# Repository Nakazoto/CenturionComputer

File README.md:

# CenturionComputer
If you are here reading this readme, most likely you are looking for the Wiki. Click the Wiki link above or the link below to get to there.

https://github.com/Nakazoto/CenturionComputer/wiki

This is just a simple backup of all the files related to the Centurion that I have stored on my HD. The Wiki itself has far more in-depth information about the Centurion and it's individual cards.

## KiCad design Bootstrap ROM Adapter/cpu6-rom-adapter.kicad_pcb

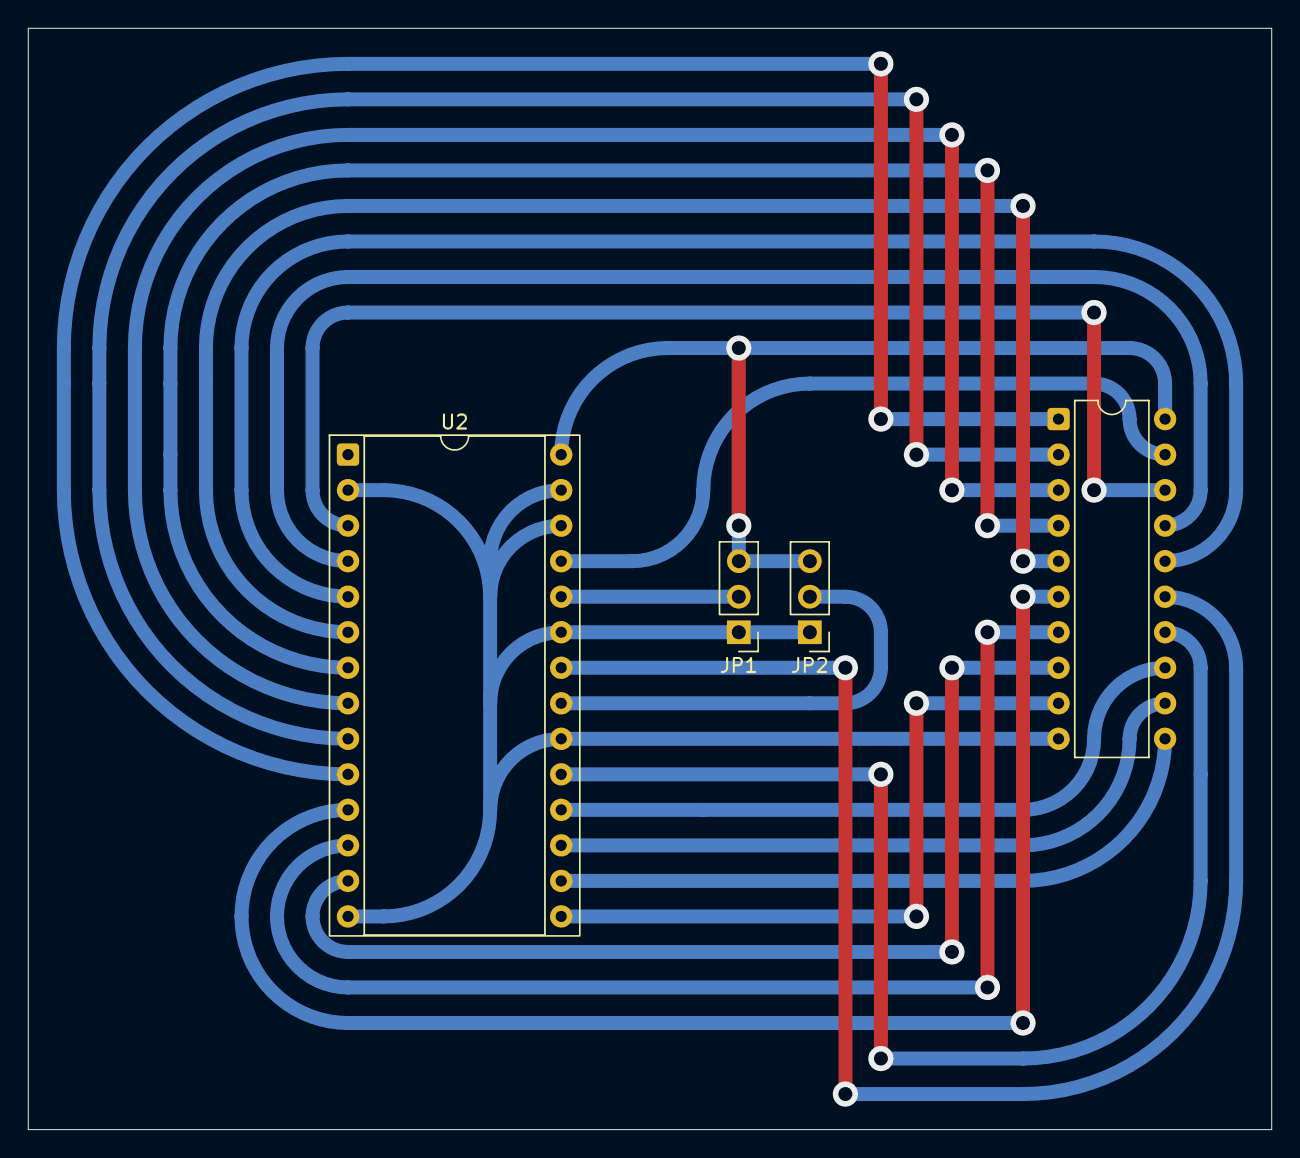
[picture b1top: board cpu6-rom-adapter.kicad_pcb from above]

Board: 2 copper layers, 88.9 x 78.7 mm, 4 parts (0 on the bottom side), 22 nets.

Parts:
J1: Conn_02x10_Counter_Clockwise; DIP-20_W7.62mm
JP1, JP2: Jumper_3_Open; PinHeader_1x03_P2.54mm_Vertical
U2: W27E257; DIP-28_W15.24mm_Socket

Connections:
/A0: J1.1, U2.10 (A0)
/A1: J1.2, U2.9 (A1)
/A2: J1.3, U2.8 (A2)
/A3: J1.4, U2.7 (A3)
/A4: J1.5, U2.6 (A4)
/A5: J1.16, U2.5 (A5)
/A6: J1.17, U2.4 (A6)
/A7: J1.18, U2.3 (A7)
/A8: J1.19, U2.25 (A8)
/A9: JP1.2 (C), U2.24 (A9)
/A10: JP2.2 (C), U2.21 (A10)
/GND: J1.10, JP1.1 (A), JP2.1 (A), U2.2 (A12), U2.14 (GND), U2.20 (~CE), U2.23 (A11), U2.26 (A13), U2.27 (A14)
/Q0: J1.6, U2.11 (Q0)
/Q1: J1.7, U2.12 (Q1)
/Q2: J1.8, U2.13 (Q2)
/Q3: J1.9, U2.15 (Q3)
/Q4: J1.11, U2.16 (Q4)
/Q5: J1.12, U2.17 (Q5)
/Q6: J1.13, U2.18 (Q6)
/Q7: J1.14, U2.19 (Q7)
/Vcc: J1.20, JP1.3 (B), JP2.3 (B), U2.28 (Vcc)
/~G: J1.15, U2.22 (~OE)

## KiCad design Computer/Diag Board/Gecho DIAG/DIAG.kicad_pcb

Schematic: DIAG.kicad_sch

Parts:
C1, C2: 150uF; CP_Axial_L25.0mm_D10.0mm_P30.00mm_Horizontal
C3: 47uF; CP_Axial_L18.0mm_D6.5mm_P25.00mm_Horizontal
C4, C5, C6, C7, C8, C9, C10, C11, C12, C13, C14, C15, C16, C17, C18, C19, C20, C21, C22, C23, C24, C25, C26, C27, C28, C29, C30, C31, C32, C33, C34, C35, C36: 100nF; C_Disc_D3.0mm_W1.6mm_P2.50mm
CR1, CR2, CR3: D; D_DO-35_SOD27_P11.43mm_Horizontal
CR4: LED; LED_D1.8mm_W1.8mm_H2.4mm_Horizontal_O6.35mm_Z1.6mm
J1, J2, J3: SW_SPDT_312; SW_Slide-03_Wuerth-WS-SLTV_10x2.5x6.4_P2.54mm
P1: Edge Connector; BUS_EE200
P2: 26 pin IDC horizontal; IDC-Header_2x13_P2.54mm_Horizontal_TB
R1, R2, R3, R4, R5, R6, R7, R8, R13, R14: 4k7; R_Axial_DIN0207_L6.3mm_D2.5mm_P11.43mm_Horizontal
R9, R10, R23: 330R; R_Axial_DIN0207_L6.3mm_D2.5mm_P11.43mm_Horizontal
R11, R12, R18: 1k; R_Axial_DIN0207_L6.3mm_D2.5mm_P11.43mm_Horizontal
R15, R16, R17: R; R_Axial_DIN0207_L6.3mm_D2.5mm_P11.43mm_Horizontal
R19, R20, R21, R22: 470R; R_Axial_DIN0207_L6.3mm_D2.5mm_P11.43mm_Horizontal
RP1, RP2: 4k7; R_Array_SIP10_cent
TP1, TP2, TP3, TP4: TestPoint; TestPoint_Hex_D2.0mm_Drill0.8mm
UA1: 74LS38; DIP-14_W7.62mm_cent
UA2, UA3, UA4, UA5, UA6: DS8835N; DIP-16_W7.62mm_cent
UA7: 74LS373; DIP-20_W7.62mm_cent
UA8: AM2907; DIP-20_W7.62mm_cent
UAB1: 74LS38; DIP-14_W7.62mm_cent
UB1: 74LS08; DIP-14_W7.62mm_cent
UB2: 74LS109; DIP-16_W7.62mm_cent
UB3, UB4: DS8835N; DIP-16_W7.62mm_cent
UB5: 74LS373; DIP-20_W7.62mm_cent
UB6: SW_DIP_x08; SW_DIP_SPSTx08_Slide_9.78x22.5mm_W8.61mm_P2.54mm_cent
UB7: 74LS37; DIP-14_W7.62mm_cent
UC1, UC7: 74LS74; DIP-14_W7.62mm_cent
UC2: 74LS161; DIP-16_W7.62mm_cent
UC3: 74LS85; DIP-16_W7.62mm_cent
UC4, UC8: 74LS08; DIP-14_W7.62mm_cent
UC5: 74LS670; DIP-16_W7.62mm_cent
UC6: 74LS38; DIP-14_W7.62mm_cent
UD1, UD7: 74LS04; DIP-14_W7.62mm_cent
UD2: 74LS688; DIP-20_W7.62mm_cent
UD3, UD4: 74LS244; DIP-20_W7.62mm_cent
UD5: Z84C00xxP; DIP-40_W15.24mm_cent_socketchip
UD6: 74LS00; DIP-14_W7.62mm_cent
UD8: 74LS74; DIP-14_W7.62mm_cent
UE1: 74LS20; DIP-14_W7.62mm_cent
UE2: 74HCT164; DIP-14_W7.62mm_cent
UE3, UE4: 74LS138; DIP-16_W7.62mm_cent
UE6, UE7: 74LS245; DIP-20_W7.62mm_cent
UE8: 74LS04; DIP-14_W7.62mm_cent
UF1, UF2, UF3, UF4, UF5, UF6: 28C16; DIP-24_W15.24mm_cent_socket
UF8: 6116; DIP-24_W15.24mm_cent_socket
UH1, UH2, UH3, UH4, UH5, UH6, UH7: 28C16; DIP-24_W15.24mm_cent_socket
UH8: 74LS155; DIP-16_W7.62mm_cent
UJ1, UJ2: 74LS259; DIP-16_W7.62mm_cent
UJ3, UJ7, UJ8: 74LS157; DIP-16_W7.62mm_cent
UJ4: 74LS04; DIP-14_W7.62mm_cent
UJ5: 74LS10; DIP-14_W7.62mm_cent
UJ6: 74LS00; DIP-14_W7.62mm_cent
UK1: 74LS109; DIP-16_W7.62mm_cent
UK2: 220/330 Divider; DIP-16_W7.62mm_cent
UK3, UK4: 74LS37; DIP-14_W7.62mm_cent
UK7: 74LS373; DIP-20_W7.62mm_cent
UK8: SW_Slide_DPDT; DPDT_diag
UL5, UL6: TIL311; DIP-14_TIL-311_diag
UL7: SW_DIP_x07; SW_DIP_SPSTx07_Slide_9.78x19.96mm_W7.62mm_P2.54mm_diag
Y1: 15MHz HC49-U; Crystal_HC49-U_Horizontal_P5.08mm

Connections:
5MHZ: UB2.12 (C), UC1.3 (C), UC2.2 (CP), UC8.8
+12V: C20.1, P1.a4, P1.b4, R15.1, TP4.1
-12V: P1.a34, P1.b34, TP1.1
A0: UA2.2 (IN0), UA2.3 (OUT0), UC5.14 (Wa), UD4.9 (O0b), UF1.8 (A0), UF2.8 (A0), UF3.8 (A0), UF4.8 (A0), UF5.8 (A0), UF6.8 (A0), UF8.8 (A0), UH1.8 (A0), UH2.8 (A0), UH3.8 (A0), UH4.8 (A0), UH5.8 (A0), UH6.8 (A0), UH7.8 (A0), UJ1.13 (D), UJ2.13 (D)
A1: UA2.5 (IN1), UA2.6 (OUT1), UC5.13 (Wb), UD4.12 (O3a), UF1.7 (A1), UF2.7 (A1), UF3.7 (A1), UF4.7 (A1), UF5.7 (A1), UF6.7 (A1), UF8.7 (A1), UH1.7 (A1), UH2.7 (A1), UH3.7 (A1), UH4.7 (A1), UH5.7 (A1), UH6.7 (A1), UH7.7 (A1), UJ1.1 (A0), UJ2.1 (A0)
A2: UA2.13 (OUT3), UA2.14 (IN3), UD4.7 (O1b), UF1.6 (A2), UF2.6 (A2), UF3.6 (A2), UF4.6 (A2), UF5.6 (A2), UF6.6 (A2), UF8.6 (A2), UH1.6 (A2), UH2.6 (A2), UH3.6 (A2), UH4.6 (A2), UH5.6 (A2), UH6.6 (A2), UH7.6 (A2), UJ1.2 (A1), UJ2.2 (A1)
A3: UA2.10 (OUT2), UA2.11 (IN2), UD4.14 (O2a), UF1.5 (A3), UF2.5 (A3), UF3.5 (A3), UF4.5 (A3), UF5.5 (A3), UF6.5 (A3), UF8.5 (A3), UH1.5 (A3), UH2.5 (A3), UH3.5 (A3), UH4.5 (A3), UH5.5 (A3), UH6.5 (A3), UH7.5 (A3), UJ1.3 (A2), UJ2.3 (A2)
A4: UA3.2 (IN0), UA3.3 (OUT0), UD4.5 (O2b), UF1.4 (A4), UF2.4 (A4), UF3.4 (A4), UF4.4 (A4), UF5.4 (A4), UF6.4 (A4), UF8.4 (A4), UH1.4 (A4), UH2.4 (A4), UH3.4 (A4), UH4.4 (A4), UH5.4 (A4), UH6.4 (A4), UH7.4 (A4), UH8.13 (A0)
A5: UA3.5 (IN1), UA3.6 (OUT1), UD2.6 (P2), UD4.16 (O1a), UF1.3 (A5), UF2.3 (A5), UF3.3 (A5), UF4.3 (A5), UF5.3 (A5), UF6.3 (A5), UF8.3 (A5), UH1.3 (A5), UH2.3 (A5), UH3.3 (A5), UH4.3 (A5), UH5.3 (A5), UH6.3 (A5), UH7.3 (A5), UH8.3 (A1)
A6: UA3.13 (OUT3), UA3.14 (IN3), UD2.8 (P3), UD4.3 (O3b), UF1.2 (A6), UF2.2 (A6), UF3.2 (A6), UF4.2 (A6), UF5.2 (A6), UF6.2 (A6), UF8.2 (A6), UH1.2 (A6), UH2.2 (A6), UH3.2 (A6), UH4.2 (A6), UH5.2 (A6), UH6.2 (A6), UH7.2 (A6)
A7: UA3.10 (OUT2), UA3.11 (IN2), UD2.11 (P4), UD4.18 (O0a), UF1.1 (A7), UF2.1 (A7), UF3.1 (A7), UF4.1 (A7), UF5.1 (A7), UF6.1 (A7), UF8.1 (A7), UH1.1 (A7), UH2.1 (A7), UH3.1 (A7), UH4.1 (A7), UH5.1 (A7), UH6.1 (A7), UH7.1 (A7)
A8: UB3.2 (IN0), UB3.3 (OUT0), UD2.4 (P1), UD3.3 (O3b), UF1.23 (A8), UF2.23 (A8), UF3.23 (A8), UF4.23 (A8), UF5.23 (A8), UF6.23 (A8), UF8.23 (A8), UH1.23 (A8), UH2.23 (A8), UH3.23 (A8), UH4.23 (A8), UH5.23 (A8), UH6.23 (A8), UH7.23 (A8)
A9: UB3.13 (OUT3), UB3.14 (IN3), UD2.13 (P5), UD3.16 (O1a), UF1.22 (A9), UF2.22 (A9), UF3.22 (A9), UF4.22 (A9), UF5.22 (A9), UF6.22 (A9), UF8.22 (A9), UH1.22 (A9), UH2.22 (A9), UH3.22 (A9), UH4.22 (A9), UH5.22 (A9), UH6.22 (A9), UH7.22 (A9)
A10: UB3.10 (OUT2), UB3.11 (IN2), UD2.15 (P6), UD3.18 (O0a), UF1.19 (A10), UF2.19 (A10), UF3.19 (A10), UF4.19 (A10), UF5.19 (A10), UF6.19 (A10), UF8.19 (A10), UH1.19 (A10), UH2.19 (A10), UH3.19 (A10), UH4.19 (A10), UH5.19 (A10), UH6.19 (A10), UH7.19 (A10)
A11: UB3.5 (IN1), UB3.6 (OUT1), UD2.17 (P7), UD3.14 (O2a), UE3.1 (A0), UE4.1 (A0)
A12: UB4.2 (IN0), UB4.3 (OUT0), UD3.5 (O2b), UE1.9, UE3.2 (A1), UE4.2 (A1)
A13: UB4.13 (OUT3), UB4.14 (IN3), UD3.12 (O3a), UE1.10, UE3.3 (A2), UE4.3 (A2)
A14: UB4.10 (OUT2), UB4.11 (IN2), UC5.5 (Ra), UD3.7 (O1b), UE1.12, UE3.5 (E2), UE4.6 (E3)
A15: UB4.5 (IN1), UB4.6 (OUT1), UC3.12 (A1), UC4.10, UC5.10 (Q1)
A16: UA4.10 (OUT2), UA4.11 (IN2), UC3.13 (A2), UC4.9, UC5.9 (Q2)
A17: UA4.13 (OUT3), UA4.14 (IN3), UC3.15 (A3), UC4.5, UC5.7 (Q3)
ACT: R18.2, UAB1.6, UE2.9 (~MR)
B15: R5.2, UB6.1, UC3.11 (B1)
B16: R13.2, UB6.2, UC3.14 (B2)
B17: RP1.8 (R7), UB6.3, UC3.1 (B3)
BUS.CYC: UB1.1, UB1.4, UB2.10 (Q), UC1.1 (~R), UC1.2 (D), UK1.12 (C)
BUSCLK: UC8.11, UE2.8 (CP)
BUSEND: UC1.12 (D), UC2.15 (TC), UK3.5
BUSY: UB1.13, UB2.15 (~R), UC1.8 (~Q), UC2.7 (CEP)
D0: UA5.3 (OUT0), UB5.4 (D1)
D1: UA5.6 (OUT1), UB5.3 (D0)
D2: UA5.13 (OUT3), UB5.17 (D6)
D3: UA5.10 (OUT2), UB5.18 (D7)
D4: UA6.3 (OUT0), UB5.14 (D5)
D5: UA6.6 (OUT1), UB5.13 (D4)
D6: UA6.13 (OUT3), UB5.8 (D3)
D7: UA6.10 (OUT2), UB5.7 (D2)
DEV0: UJ2.4 (Q0), UK4.4, UK4.5
DEV1: UJ2.5 (Q1), UK4.1, UK4.2
DLE: UB5.11 (LE), UD7.1, UJ7.7 (Zb)
DMA7: P2.7, UK2.13 (R12)
DRDY: UA7.8 (D3), UD1.9, UD1.10
EN: UJ2.6 (Q2), UK3.9, UK3.10
GND: C1.2, C2.2, C3.2, C4.2, C5.2, C6.2, C7.2, C8.2, C9.2, C10.2, C11.2, C12.2, C13.2, C14.2, C15.2, C16.2, C17.2, C18.2, C19.2, C20.2, C21.2, C22.2, C23.2, C24.2, C25.2, C26.2, C27.2, C28.2, C29.2, C30.2, C31.2, C32.2, C33.2, C34.2, C35.2, C36.2, J1.2 (C), P1.a1, P1.a36, P1.b1, P1.b36, P2.14, P2.15, P2.16, P2.17, P2.18, P2.19, P2.20, P2.21, P2.22, P2.23, P2.24, P2.25, P2.26, R16.2, TP2.1, UA1.7 (GND), UA2.8 (GND), UA3.8 (GND), UA4.8 (GND), UA5.7 (REN), UA5.8 (GND), UA6.7 (REN), UA6.8 (GND), UA7.10 (GND), UA8.5 (GND1), UA8.15 (GND2), UAB1.7 (GND), UB1.7 (GND), UB2.8 (GND), UB3.8 (GND), UB4.8 (GND), UB5.10 (GND), UB6.9, UB6.14, UB6.15, UB6.16, UB7.7 (GND), UC1.7 (GND), UC2.8 (GND), UC3.2 (Ia<b), UC3.4 (Ia>b), UC3.8 (GND), UC4.7 (GND), UC5.8 (GND), UC6.7 (GND), UC7.7 (GND), UC8.7 (GND), UD1.7 (GND), UD2.7 (R2), UD2.9 (R3), UD2.10 (GND), UD2.12 (R4), UD2.14 (R5), UD2.16 (R6), UD2.18 (R7), UD3.10 (GND), UD4.10 (GND), UD5.29 (GND), UD6.7 (GND), UD7.7 (GND), UD8.7 (GND), UE1.7 (GND), UE2.7 (GND), UE3.8 (GND), UE4.5 (E2), UE4.8 (GND), UE6.10 (GND), UE7.10 (GND), UE8.7 (GND), UF1.12 (GND), UF1.20 (~OE), UF2.12 (GND), UF2.20 (~OE), UF3.12 (GND), UF3.20 (~OE), UF4.12 (GND), UF4.20 (~OE), UF5.12 (GND), UF5.20 (~OE), UF6.12 (GND), UF6.20 (~OE), UF8.12 (GND), UF8.20 (~OE), UH1.12 (GND), UH1.20 (~OE), UH2.12 (GND), UH2.20 (~OE), UH3.12 (GND), UH3.20 (~OE), UH4.12 (GND), UH4.20 (~OE), UH5.12 (GND), UH5.20 (~OE), UH6.12 (GND), UH6.20 (~OE), UH7.12 (GND), UH7.20 (~OE), UH8.8 (GND), UJ1.8 (GND), UJ2.8 (GND), UJ3.8 (GND), UJ3.14 (I0d), UJ3.15 (E), UJ4.7 (GND), UJ5.7 (GND), UJ6.7 (GND), UJ7.8 (GND), UJ7.15 (E), UJ8.8 (GND), UJ8.15 (E), UK1.8 (GND), UK2.8 (COM2), UK3.7 (GND), UK4.7 (GND), UK7.10 (GND), UK8.1 (A), UK8.6 (C), UL5.7 (GND), UL6.7 (GND), UL7.8, UL7.9, UL7.10, UL7.11, UL7.12, UL7.13, UL7.14
ID0: RP1.4 (R3), UA5.2 (IN0), UA7.2 (O0), UB5.5 (O1), UC5.15 (D1), UE6.11 (B7), UE7.11 (B7), UK7.19 (O7), UL6.3 (A)
ID1: RP1.2 (R1), UA5.5 (IN1), UA7.6 (O2), UB5.2 (O0), UC5.1 (D2), UE6.12 (B6), UE7.12 (B6), UK7.16 (O6), UL6.2 (B)
ID2: RP1.5 (R4), UA5.14 (IN3), UA7.19 (O7), UB5.16 (O6), UC5.2 (D3), UE6.14 (B4), UE7.14 (B4), UK7.15 (O5), UL6.13 (C)
ID3: RP1.3 (R2), UA5.11 (IN2), UA7.12 (O4), UB5.19 (O7), UC5.3 (D4), UE6.17 (B1), UE7.17 (B1), UK7.12 (O4), UL6.12 (D)
ID4: RP1.7 (R6), UA6.2 (IN0), UA7.9 (O3), UA8.3 (IN0), UB5.15 (O5), UE6.18 (B0), UE7.18 (B0), UK7.2 (O0), UL5.3 (A)
ID5: RP1.9 (R8), UA6.5 (IN1), UA7.15 (O5), UA8.7 (IN1), UB5.12 (O4), UE6.16 (B2), UE7.16 (B2), UK7.5 (O1), UL5.2 (B)
ID6: RP1.10 (R9), UA6.14 (IN3), UA7.5 (O1), UA8.13 (IN2), UB5.9 (O3), UE6.15 (B3), UE7.15 (B3), UK7.6 (O2), UL5.13 (C)
ID7: RP1.6 (R5), UA6.11 (IN2), UA7.16 (O6), UA8.17 (IN3), UB5.6 (O2), UE6.13 (B5), UE7.13 (B5), UK7.9 (O3), UL5.12 (D)
MD0: UE7.9 (A7), UF1.9 (I/O0), UF2.9 (I/O0), UF3.9 (I/O0), UF4.9 (I/O0), UF5.9 (I/O0), UF6.9 (I/O0), UF8.9 (I/O0), UH1.9 (I/O0), UH2.9 (I/O0), UH3.9 (I/O0), UH4.9 (I/O0), UH5.9 (I/O0), UH6.9 (I/O0), UH7.9 (I/O0)
MD1: UE7.8 (A6), UF1.10 (I/O1), UF2.10 (I/O1), UF3.10 (I/O1), UF4.10 (I/O1), UF5.10 (I/O1), UF6.10 (I/O1), UF8.10 (I/O1), UH1.10 (I/O1), UH2.10 (I/O1), UH3.10 (I/O1), UH4.10 (I/O1), UH5.10 (I/O1), UH6.10 (I/O1), UH7.10 (I/O1)
MD2: UE7.6 (A4), UF1.11 (I/O2), UF2.11 (I/O2), UF3.11 (I/O2), UF4.11 (I/O2), UF5.11 (I/O2), UF6.11 (I/O2), UF8.11 (I/O2), UH1.11 (I/O2), UH2.11 (I/O2), UH3.11 (I/O2), UH4.11 (I/O2), UH5.11 (I/O2), UH6.11 (I/O2), UH7.11 (I/O2)
MD3: UE7.3 (A1), UF1.13 (I/O3), UF2.13 (I/O3), UF3.13 (I/O3), UF4.13 (I/O3), UF5.13 (I/O3), UF6.13 (I/O3), UF8.13 (I/O3), UH1.13 (I/O3), UH2.13 (I/O3), UH3.13 (I/O3), UH4.13 (I/O3), UH5.13 (I/O3), UH6.13 (I/O3), UH7.13 (I/O3)
MD4: UE7.2 (A0), UF1.14 (I/O4), UF2.14 (I/O4), UF3.14 (I/O4), UF4.14 (I/O4), UF5.14 (I/O4), UF6.14 (I/O4), UF8.14 (I/O4), UH1.14 (I/O4), UH2.14 (I/O4), UH3.14 (I/O4), UH4.14 (I/O4), UH5.14 (I/O4), UH6.14 (I/O4), UH7.14 (I/O4)
MD5: UE7.4 (A2), UF1.15 (I/O5), UF2.15 (I/O5), UF3.15 (I/O5), UF4.15 (I/O5), UF5.15 (I/O5), UF6.15 (I/O5), UF8.15 (I/O5), UH1.15 (I/O5), UH2.15 (I/O5), UH3.15 (I/O5), UH4.15 (I/O5), UH5.15 (I/O5), UH6.15 (I/O5), UH7.15 (I/O5)
MD6: UE7.5 (A3), UF1.16 (I/O6), UF2.16 (I/O6), UF3.16 (I/O6), UF4.16 (I/O6), UF5.16 (I/O6), UF6.16 (I/O6), UF8.16 (I/O6), UH1.16 (I/O6), UH2.16 (I/O6), UH3.16 (I/O6), UH4.16 (I/O6), UH5.16 (I/O6), UH6.16 (I/O6), UH7.16 (I/O6)
MD7: UE7.7 (A5), UF1.17 (I/O7), UF2.17 (I/O7), UF3.17 (I/O7), UF4.17 (I/O7), UF5.17 (I/O7), UF6.17 (I/O7), UF8.17 (I/O7), UH1.17 (I/O7), UH2.17 (I/O7), UH3.17 (I/O7), UH4.17 (I/O7), UH5.17 (I/O7), UH6.17 (I/O7), UH7.17 (I/O7)
MMIO15: UA4.3 (OUT0), UE1.13
MREQ: UB2.4 (C), UC4.11, UJ5.5, UJ5.9, UJ6.5
unnamed: C3.1, CR1.2 (A), RP2.2 (R1), UC4.1, UC4.2, UK8.2 (B), UK8.5 (B)
unnamed: CR2.2 (A), CR3.2 (A), R15.2
unnamed: CR2.1 (K), R16.1, R17.1, UE8.8, UE8.10, UE8.12
unnamed: CR4.2 (A), R23.2
unnamed: CR4.1 (K), UD3.9 (O0b)
unnamed: J1.1 (B), UE3.4 (E1), UE4.4 (E1)
unnamed: J3.1 (B), UJ6.10
unnamed: J3.2 (C), UJ4.10
unnamed: P1.a30, P1.b30
unnamed: P1.a33, P1.b33, R1.2
unnamed: R9.2, UB7.4, UB7.5, Y1.2
unnamed: R10.1, UB7.8, UD7.13, Y1.1
unnamed: R9.1, R10.2, UB7.6, UB7.9, UB7.10
unnamed: RP2.3 (R2), UK7.3 (D0), UL7.5
unnamed: RP2.4 (R3), UK7.18 (D7), UL7.1
unnamed: RP2.5 (R4), UK7.17 (D6), UL7.2
unnamed: RP2.6 (R5), UK7.4 (D1), UL7.6
unnamed: RP2.7 (R6), UK7.7 (D2), UL7.7
unnamed: RP2.8 (R7), UK7.14 (D5), UL7.3
unnamed: RP2.9 (R8), UK7.13 (D4), UL7.4
unnamed: UA4.2 (IN0), UC4.6
unnamed: UA7.11 (LE), UD6.11
unnamed: UB1.2, UD1.2
unnamed: UB1.9, UB2.6 (Q)
unnamed: UB1.11, UB2.1 (~R)
unnamed: UB1.8, UB2.14 (J)
unnamed: UB6.13, UB7.3
unnamed: UC1.5 (Q), UC1.13 (~R), UC2.1 (~MR)
unnamed: UB1.12, UC2.9 (~PE), UD1.8
unnamed: UC4.4, UC4.8
unnamed: UC4.13, UE8.6
unnamed: UC5.6 (Q4), UD6.1
unnamed: UC7.3 (C), UC7.11 (C), UD7.12
unnamed: R11.2, UC7.2 (D), UC7.4 (~S), UC7.10 (~S), UC7.13 (~R)
unnamed: UC7.5 (Q), UC7.12 (D)
unnamed: UC7.1 (~R), UC7.8 (~Q)
unnamed: UC7.9 (Q), UC8.9, UC8.10, UD7.3, UD8.11 (C)
unnamed: UD1.6, UE1.1, UE1.2
unnamed: UD3.2 (I0a), UD5.40 (A_{10})
unnamed: UD3.11 (I0b), UD5.18 (~HALT)
unnamed: UD3.4 (I1a), UD5.39 (A_{9})
unnamed: UD3.13 (I1b), UD5.4 (A_{14})
unnamed: UD3.6 (I2a), UD5.1 (A_{11})
unnamed: UD3.15 (I2b), UD5.2 (A_{12})
unnamed: UD3.8 (I3a), UD5.3 (A_{13})
unnamed: UD3.17 (I3b), UD5.38 (A_{8})
unnamed: UD4.2 (I0a), UD5.37 (A_{7})
unnamed: UD4.11 (I0b), UD5.30 (A_{0})
unnamed: UD4.4 (I1a), UD5.35 (A_{5})
unnamed: UD4.13 (I1b), UD5.32 (A_{2})
unnamed: UD4.6 (I2a), UD5.33 (A_{3})
unnamed: UD4.15 (I2b), UD5.34 (A_{4})
unnamed: UD4.8 (I3a), UD5.31 (A_{1})
unnamed: UD4.17 (I3b), UD5.36 (A_{6})
unnamed: UD5.14 (D_{0}), UE6.9 (A7)
unnamed: UD5.15 (D_{1}), UE6.8 (A6)
unnamed: UD5.12 (D_{2}), UE6.6 (A4)
unnamed: UD5.8 (D_{3}), UE6.3 (A1)
unnamed: UD5.7 (D_{4}), UE6.2 (A0)
unnamed: UD5.9 (D_{5}), UE6.4 (A2)
unnamed: UD5.10 (D_{6}), UE6.5 (A3)
unnamed: UD5.13 (D_{7}), UE6.7 (A5)
unnamed: UD5.19 (~MREQ), UE8.5
unnamed: UD5.21 (~RD), UE8.1
unnamed: UC4.12, UD5.28 (~RFSH)
unnamed: UD6.3, UD6.4
unnamed: UD6.5, UD7.6
unnamed: UD6.8, UD7.5
unnamed: UD6.13, UD7.2
unnamed: UD7.8, UJ6.4
unnamed: UD8.8 (~Q), UD8.12 (D)
unnamed: UD8.9 (Q), UE8.9, UE8.11, UE8.13
unnamed: UE1.6, UE2.1 (DSA)
unnamed: UE2.3 (Q0), UJ5.13, UJ6.2
unnamed: UAB1.9, UAB1.10, UE2.5 (Q2), UJ4.13, UJ6.12
unnamed: UD6.10, UE4.9 (O6)
unnamed: UD6.9, UE4.7 (O7)
unnamed: UE7.1 (A->B), UH8.1 (Ea1), UJ8.7 (Zb)
unnamed: UH8.2 (Ea2), UH8.15 (Eb2), UJ8.9 (Zc)
unnamed: UH8.14 (Eb1), UJ4.3, UJ8.4 (Za)
unnamed: UH8.9 (Q0b), UJ2.14 (E)
unnamed: UH8.10 (Q1b), UL5.5 (LE), UL6.5 (LE)
unnamed: UD6.2, UJ1.4 (Q0)
unnamed: UC6.1, UJ1.5 (Q1)
unnamed: UC6.5, UJ1.6 (Q2)
unnamed: UC6.12, UJ1.7 (Q3)
unnamed: UJ1.9 (Q4), UJ3.1 (S), UK1.14 (J), UK3.2, UK4.9, UK4.10
unnamed: UJ1.10 (Q5), UK1.15 (~R)
unnamed: UJ2.7 (Q3), UL5.8 (OE), UL6.8 (OE)
unnamed: R21.1, UJ2.9 (Q4)
unnamed: R22.1, UJ2.10 (Q5)
unnamed: R19.1, UJ2.11 (Q6)
unnamed: R20.1, UJ2.12 (Q7)
unnamed: UJ3.11 (I0c), UJ5.6
unnamed: UJ3.3 (I1a), UJ4.2
unnamed: UJ3.6 (I1b), UJ3.13 (I1d), UJ4.6
unnamed: UJ3.12 (Zd), UK3.4
unnamed: UJ4.4, UJ6.9
unnamed: UJ4.8, UJ5.1
unnamed: UJ4.12, UJ5.2
unnamed: UJ5.8, UJ7.2 (I0a)
unnamed: UJ6.6, UJ7.14 (I0d)
unnamed: UJ6.11, UJ7.3 (I1a)
unnamed: UJ6.3, UJ7.13 (I1d)
unnamed: UJ5.12, UJ8.3 (I1a)
unnamed: UK1.10 (Q), UK3.12, UK3.13
unnamed: R20.2, UL5.4 (L)
unnamed: R19.2, UL5.10 (R)
unnamed: R22.2, UL6.4 (L)
unnamed: R21.2, UL6.10 (R)
PRE: UA1.1, UA1.2, UA1.12, UA1.13, UC3.6 (Oa=b), UD1.5, UJ6.1
RD: UAB1.1, UB1.6, UJ7.5 (I0b)
RDIN: UD1.4, UJ4.9, UJ6.13, UJ7.10 (I1c), UJ8.6 (I1b)
START: UB1.10, UJ3.4 (Za)
VCC: C1.1, C2.1, C4.1, C5.1, C6.1, C7.1, C8.1, C9.1, C10.1, C11.1, C12.1, C13.1, C14.1, C15.1, C16.1, C17.1, C18.1, C19.1, C21.1, C22.1, C23.1, C24.1, C25.1, C26.1, C27.1, C28.1, C29.1, C30.1, C31.1, C32.1, C33.1, C34.1, C35.1, C36.1, CR1.1 (K), CR3.1 (K), J2.3 (A), J3.3 (A), P1.a2, P1.a35, P1.b2, P1.b35, R1.1, R2.1, R3.1, R4.1, R5.1, R6.1, R7.1, R8.1, R11.1, R12.1, R13.1, R14.1, R18.1, R23.1, RP1.1 (common), RP2.1 (common), TP3.1, UA1.14 (VCC), UA2.16 (VCC), UA3.16 (VCC), UA4.16 (VCC), UA5.16 (VCC), UA6.16 (VCC), UA7.20 (VCC), UA8.20 (VCC), UAB1.14 (VCC), UB1.14 (VCC), UB2.5 (~S), UB2.11 (~S), UB2.13 (~K), UB2.16 (VCC), UB3.16 (VCC), UB4.16 (VCC), UB5.20 (VCC), UB7.14 (VCC), UC1.4 (~S), UC1.10 (~S), UC1.14 (VCC), UC2.3 (D0), UC2.4 (D1), UC2.5 (D2), UC2.6 (D3), UC2.10 (CET), UC2.16 (VCC), UC3.9 (B0), UC3.16 (VCC), UC4.14 (VCC), UC5.16 (VCC), UC6.14 (VCC), UC7.14 (VCC), UC8.14 (VCC), UD1.14 (VCC), UD2.3 (R0), UD2.5 (R1), UD2.20 (VCC), UD3.20 (VCC), UD4.20 (VCC), UD5.11 (V_{CC}), UD5.25 (~BUSREQ), UD6.14 (VCC), UD7.14 (VCC), UD8.10 (~S), UD8.13 (~R), UD8.14 (VCC), UE1.14 (VCC), UE2.14 (VCC), UE3.6 (E3), UE3.16 (VCC), UE4.16 (VCC), UE6.20 (VCC), UE7.20 (VCC), UE8.14 (VCC), UF1.24 (VCC), UF2.24 (VCC), UF3.24 (VCC), UF4.24 (VCC), UF5.24 (VCC), UF6.24 (VCC), UF8.24 (VCC), UH1.24 (VCC), UH2.24 (VCC), UH3.24 (VCC), UH4.24 (VCC), UH5.24 (VCC), UH6.24 (VCC), UH7.24 (VCC), UH8.16 (VCC), UJ1.16 (VCC), UJ2.16 (VCC), UJ3.2 (I0a), UJ3.10 (I1c), UJ3.16 (VCC), UJ4.14 (VCC), UJ5.14 (VCC), UJ6.14 (VCC), UJ7.6 (I1b), UJ7.16 (VCC), UJ8.16 (VCC), UK1.11 (~S), UK1.13 (~K), UK1.16 (VCC), UK2.16 (COM1), UK3.14 (VCC), UK4.14 (VCC), UK7.20 (VCC), UL5.1 (SUP), UL5.14 (VCC), UL6.1 (SUP), UL6.14 (VCC)
WT: UAB1.12, UB1.3, UK3.1
Z80: UA2.7 (REN), UA3.7 (REN), UA4.7 (REN), UAB1.2, UAB1.13, UB3.7 (REN), UB4.7 (REN), UC6.2, UC6.4, UC6.13, UD1.12
ZA15: UC5.4 (Rb), UD5.5 (A_{15})
ZC: R17.2, UD5.6 (CLK)
ZEXT: UB2.2 (J), UB2.3 (~K), UD6.6, UD7.9, UJ5.4, UJ5.11
ZRD: UE8.2, UE8.3, UJ3.5 (I0b), UJ5.3, UJ8.5 (I0b)
ZR/~W: UB1.5, UD1.1, UJ3.7 (Zb)
ZWT: UE6.1 (A->B), UE8.4, UJ5.10
Z~R/W: UJ3.9 (Zc), UJ7.11 (I0c)
~5MHZ: UB7.1, UB7.2, UC1.11 (C), UD7.4
~AB0: P1.b5, UA2.1 (BUS0)
~AB1: P1.b6, UA2.4 (BUS1)
~AB2: P1.b7, UA2.15 (BUS3)
~AB3: P1.b8, UA2.12 (BUS2)
~AB4: P1.b9, UA3.1 (BUS0)
~AB5: P1.b10, UA3.4 (BUS1)
~AB6: P1.b11, UA3.15 (BUS3)
~AB7: P1.b12, UA3.12 (BUS2)
~AB8: P1.b13, UB3.1 (BUS0)
~AB9: P1.b14, UB3.15 (BUS3)
~AB10: P1.b15, UB3.12 (BUS2)
~AB11: P1.b16, UB3.4 (BUS1)
~AB12: P1.b17, UB4.1 (BUS0)
~AB13: P1.b18, UB4.15 (BUS3)
~AB14: P1.b19, UB4.12 (BUS2)
~AB15: P1.a23, UB4.4 (BUS1)
~AB16: P1.a24, UA4.12 (BUS2)
~AB17: P1.a25, UA4.15 (BUS3)
~APRE: P1.a11, R2.2, UA1.3, UA1.11, UA7.14 (D5)
~BUSY: P1.a10
~CL0: P1.a18, UA8.4 (BUS0)
~CL1: P1.a19, UA8.6 (BUS1)
~CL2: P1.a20, UA8.14 (BUS2)
~CL3: P1.a21, UA8.16 (BUS3)
~CLK: P1.b31, UB6.4, UC8.12, UC8.13
~DB0: P1.b21, UA5.1 (BUS0)
~DB1: P1.b22, UA5.4 (BUS1)
~DB2: P1.b23, UA5.15 (BUS3)
~DB3: P1.b24, UA5.12 (BUS2)
~DB4: P1.b25, UA6.1 (BUS0)
~DB5: P1.b26, UA6.4 (BUS1)
~DB6: P1.b27, UA6.15 (BUS3)
~DB7: P1.b28, UA6.12 (BUS2)
~DBP: P1.b29, UC6.3
~DLOE: UB5.1 (OE), UJ7.9 (Zc)
~DMA.ACT: P2.2, UK4.8
~DMA.DEV0: P2.3, UK4.6
~DMA.DEV1: P2.4, UK4.3
~DMA.END: P2.5, UK3.11
~DMA.EN: P2.6, UK3.8
~DMA.INTR: P2.12, UA7.4 (D1), UK2.10 (R9)
~DMA.RDRDY: P2.8, UK3.6
~DMA.REQ: P2.13, UD5.17 (~NMI), UK2.9 (R8)
~DMA.R/W: P2.11, UJ4.5, UK2.11 (R10)
~DMA.START: P2.10, UJ4.1, UK2.12 (R11)
~DMA.WTRDY: P2.9, UK3.3
~DOUT: UA5.9 (WEN), UA6.9 (WEN), UJ7.4 (Za)
~DRDY: P1.a8, UAB1.8, UD1.11
~IACK: P1.a29, UC6.11, UD6.12
~INR0: P1.a16, R6.2, UA7.3 (D0)
~INR1: P1.a13, R7.2, UA7.7 (D2)
~INR2: P1.a14, R4.2, UA7.18 (D7)
~INR3: P1.a15, R3.2, UA7.13 (D4)
~INTR: P1.a27, R14.2, UD5.16 (~INT)
~IOADDR: UD2.19 (P=R), UE1.4, UE1.5, UJ8.10 (I1c)
~IORQ: UD5.20 (~IORQ), UJ8.11 (I0c)
~MEN: J1.3 (A), UE7.19 (CE), UJ7.12 (Zd)
~MMIO15: P1.b20, UA4.1 (BUS0)
~MMIO: UC3.10 (A0), UD2.1 (G), UE1.8
~MRST: P1.b32, UC6.6
~PE: P1.a28, R8.2, UA7.17 (D6)
~R0: UE3.15 (O0), UF1.18 (~CE)
~R1: UE3.14 (O1), UF2.18 (~CE)
~R2: UE3.13 (O2), UF3.18 (~CE)
~R3: UE3.12 (O3), UF4.18 (~CE)
~R4: UE3.11 (O4), UF5.18 (~CE)
~R5: UE3.10 (O5), UF6.18 (~CE)
~R6: UE3.9 (O6), UH1.18 (~CE)
~R7: UE3.7 (O7), UF8.18 (~CE), UJ4.11
~R8: UE4.15 (O0), UH2.18 (~CE)
~R9: UE4.14 (O1), UH3.18 (~CE)
~R10: UE4.13 (O2), UH4.18 (~CE)
~R11: UE4.12 (O3), UH5.18 (~CE)
~R12: UE4.11 (O4), UH6.18 (~CE)
~R13: UE4.10 (O5), UH7.18 (~CE)
~RAMW: UF1.21 (~WE), UF2.21 (~WE), UF3.21 (~WE), UF4.21 (~WE), UF5.21 (~WE), UF6.21 (~WE), UF8.21 (~WE), UH1.21 (~WE), UH2.21 (~WE), UH3.21 (~WE), UH4.21 (~WE), UH5.21 (~WE), UH6.21 (~WE), UH7.21 (~WE), UJ6.8
~RDDIP: UH8.6 (Q1a), UK7.1 (OE), UK7.11 (LE)
~RDIN: P1.a6, UAB1.3, UAB1.4, UD1.3
~RDSYS: UA7.1 (OE), UH8.4 (Q3a)
~SCLR: J2.1 (B), UJ1.15 (Clr), UJ2.15 (Clr)
~SETCL/PG: UA8.19 (DRCP), UC5.12 (~Ew), UH8.12 (Q3b)
~TRIG: J2.2 (C), UC4.3, UD5.26 (~RESET), UK7.8 (D3)
~WTIN: P1.a7, UAB1.5, UAB1.11
~Z80IO: UH8.11 (Q2b), UJ1.14 (E)
~Z80: R12.2, UA2.9 (WEN), UA3.9 (WEN), UA4.9 (WEN), UA8.9 (~BE), UB3.9 (WEN), UB4.9 (WEN), UB6.8, UC3.3 (Ia=b), UC5.11 (~Er), UD1.13, UD2.2 (P0), UD3.1 (OEa), UD3.19 (OEb), UD4.1 (OEa), UD4.19 (OEb), UE2.2 (DSB), UE6.19 (CE), UJ7.1 (S), UJ8.1 (S)
~ZWAIT: UB2.7 (~Q), UD5.24 (~WAIT)
~ZWR: UD5.22 (~WR), UJ8.2 (I0a)

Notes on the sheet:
DMA Read
bodged to VCC, Z80 mode TRIG low should reset
IO Write
Unstuffed A7: LS373 Done A8: AM2907 Done B1: LS08 (?) B2: LS109 B7: LS37 C1: LS74 C2: LS161 C5: LS670 C6: LS38 C7: LS74 D3: LS244 Done D4: LS244 Done D5: Z80 D6: LS00 D7: LS04 D8: LS74 E6: LS245 E8: LS04 J1: LS259 J3: LS157 K1: LS109 K2: Resistor pack (220/330 divider Bourns 4116R-3-221/331LF) K3: 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
DMA
high = internal mem
Z80 RD (DMA inhibits) or CPU6 WT, put contents of latch on internal data bus
unpopulated
Z80 WT or CPU6 RD - put data on the bus
unpolulated
~{WR}
J1 259 O3
external?
If it's an internal memory access and it's valid then enable the buffer
bodged to ground
Z80 RD, open latch data from bus, close it when RD goes low
RAM
2.5MHz
Z80 IO read
J1 259 O1
mouser 611-F2UOA01AAU or similar
low force external
J1 259 O2
IO Read
~{IO}
internal?

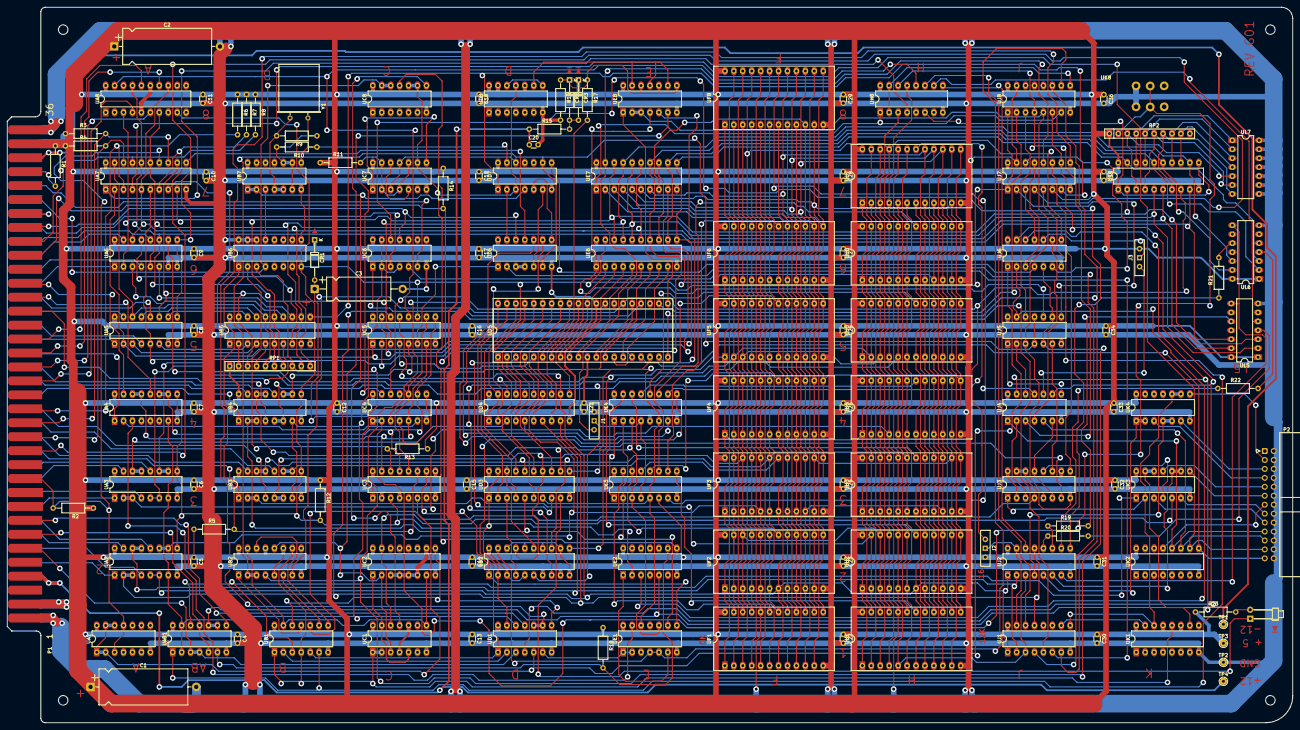
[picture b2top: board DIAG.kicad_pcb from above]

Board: 2 copper layers, 365.1 x 203.2 mm, 146 parts (0 on the bottom side), 273 nets.

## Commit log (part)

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2022-03-23 Redesign Time
2022-03-27 3/27 Update of Centurion Stuff
2022-04-03 2022/4/3 Update
2022-04-04 2022/4/4 Update
2022-04-10 2022/4/9 update
2022-04-11 2022/4/10 Update
2022-04-16 2022/4/16 Update
2022-04-20 2022/4/19 Update
2022-04-24 2022/4/24 Update
2022-04-25 2022/4/25 Update
2022-05-01 2022/5/1 Update
2022-05-03 2022/5/2 Update
2022-05-07 2022/5/6 Update
2022-05-07 2022/5/7 Update
2022-05-08 2022/5/8 Update
2022-05-09 2022/5/9 Update
2022-05-11 2022/5/11
2022-05-11 2022/05/11 Update
2022-05-13 2022/5/13 Update
2022-05-15 2022/5/15 Update
2022-05-16 2022/5/16 Update
2022-05-18 2022/5/18 Update
2022-05-20 2022/5/19 Update
2022-05-20 2022/5/20 Update
2022-05-21 2022/5/21 Update
2022-05-23 2022/5/23 Update
2022-05-25 2022/5/25
2022-05-27 2022/5/26 Update
2022-05-27 Revert "2022/5/26 Update"
    This reverts commit 20a8666ca6e3ef23400b766728823656f6aa38b8.
2022-05-31 2022/5/31 Update
2022-06-03 2022/6/3 Update
2022-06-06 2022/6/6 Update
2022-06-07 2020/6/7 update
2022-06-07 2022/6/7 Update
2022-06-14 2022/6/14
2022-06-14 2022/6/14 Update
2022-06-22 2022/6/21
2022-06-27 2022/6/27
2022-06-29 2022/6/29
2022-06-30 2022/6/30
2022-07-04 2022/7/4
2022-07-06 2022/7/5
2022-07-08 2022/7/7
2022-07-09 2022/07/09
2022-07-15 2022/7/15
2022-07-16 2022/7/16
2022-07-23 2022/7/23
2022-07-25 2022/7/25
2022-07-29 2022/7/28
2022-07-30 2022/7/30
2022-08-03 2022/8/3
2022-08-11 2022/8/10
2022-08-22 2022/8/21
2022-09-13 2022/9/12
2022-09-13 2022/9/13
2022-09-15 2022/9/15
2022-09-18 2022/9/17
2022-09-18 2022/9/18
2022-09-19 2022/9/19
2022-09-21 2022/9/20
2022-09-22 2022/9/22
2022-09-26 2022/9/26
2022-09-28 2022/9/28
2022-10-03 2022/10/3
2022-10-04 2022/10/4
2022-10-05 2022/10/5
2022-10-07 2022/10/7
2022-10-12 2022/10/12
2022-10-17 2022/10/16
2022-10-17 2022/10/17
2022-10-28 2022/10/28
2022-11-13 2022/11/12
2022-11-13 Create font
2022-11-28 2022/11/27
2022-11-28 Backplane/Schematics: Annotate system bus signals
    The CPU provides two different sets of high address lines: one for addressing
    and another for indication. This makes the schematic confusing, and with so
    many unnamed wires it's just hard to read. Add labels for the top part of CPU
    slot, change labels on the bottom to conform to Meisaka's notation. Also add a
    couple of labels to front panel connector (two LED lines), makes it easier to
    verify things.
2022-12-02 2022/12/2
2022-12-11 2022/12/11
2022-12-30 2022/12/30
2023-01-02 2023/1/2
2023-01-16 2023/1/15
2023-01-21 2023/0121
2023-01-22 2022/1/22
2023-01-24 2022/1/23
2023-01-24 2023/1/24
2023-01-27 2022/1/27
2023-01-28 2022/1/28
2023-02-02 2022/2/2
2023-02-03 2023/2/2
2023-02-04 2023/2/4
2023-02-05 2022/2/4
2023-02-20 2023/2/20
2023-02-21 2023/2/21
2023-03-03 2023/3/3
2023-03-09 2023/3/9
2023-03-15 2022/3/15
2023-03-18 2023/3/18
2023-04-04 2023/4/4
2023-04-10 2023/4/10
2023-04-24 2023/4/24
2023-04-29 2023/4/29
2023-04-30 2023/4/30
2023-05-01 2023/5/1
2023-05-08 2023/5/7
2023-05-19 2023/5/19
2023-05-20 2023/5/20
2023-05-30 2023/5/30
2023-05-31 2023/5/31
2023-06-04 2023/6/3
2023-06-04 2023/6/4
2023-06-08 2023/6/8
2023-06-13 2023/6/13
2023-07-04 2023/7/3
2023-07-13 2023/7/13
2023-07-27 2023/7/27
2023-09-03 2023/9/3
2023-09-04 2023/9/4
2023-09-14 2023/9/13
2023-09-15 2023/9/15
2023-09-17 2023/9/16
2023-09-18 2023/9/18
2023-09-19 2023/9/19
2023-09-20 2023/9/20
2023-09-21 2023/9/21
2023-09-22 2023/9/22
2023-09-23 2023/9/23
2023-09-25 2023/9/25
2023-09-27 2023/9/26
2023-10-01 2023/10/1
2023-10-02 2023/10/01
2023-10-02 2023/10/2
2023-10-02 2023/10/02
2023-10-03 2023/10/03
2023-10-06 2023/10/06
2023-10-29 2023/10/29
2023-11-21 2023/11/20
2023-11-21 2023/11/21
2023-11-29 2023/11/28
2023-12-04 2023/12/04
2023-12-06 2023/12/06
2023-12-13 2023/12/12
2023-12-13 2023/12/13
2023-12-17 2023/12/16
2024-01-31 2024/1/31
2024-02-27 2024/2/27
2024-03-04 2024/3/4
2024-04-17 2024/4/17
2024-05-12 2024/5/11
2024-05-16 2024/5/15
2024-05-23 2024/5/23
2024-05-24 2024/5/24
2024-05-27 2024/5/26
2024-05-27 2024/5/27
2024-05-28 2024/5/28
2024-06-09 2024/6/9
2024-06-30 BF - Play with centurion assembler
2024-06-30 BF - ZUB in progress
2024-07-01 BF - a few zub changes
2024-07-04 BF - Assembly bits and bobs
2024-07-09 2024/7/9
2024-08-10 2024/8/10
2024-08-22 20240821
2024-09-09 2024/9/8
2024-10-07 2024/10/07
2024-10-08 2024/10/08
2024-10-20 2024/10/19
2024-10-20 2024/10/20
2024-12-27 added basic screenshot for EtchedPixels CLI emulator
2024-12-27 remove OSX specific metadata files
2025-03-04 2025/03/03
2025-03-20 2025/3/20
2025-03-20 Diag board/Schematics: Fix and improve
    Give more appropriate names to signals, according to our up to date
    understanding. Add some comments, helping to understand board's workings.
    Bugfix: WR and RD signal names were swapped on the bus connector.
2025-07-27 2025/7/27
2025-12-11 2025/12/17
2026-03-03 2026/3/3
